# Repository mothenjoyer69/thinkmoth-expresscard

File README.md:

# ThinkMoth Expresscard to NVMe 
An ExpressCard to NVMe adapter, except this one actually ships! 

The ThinkMoth ExpressCard to NVMe is a low cost, open source adapter for using an M.2 2230/2242 NVMe SSD in an ExpressCard34/54 socket. It features a microSD card slot to enable booting from the SSD, and optional status LEDs for SD and PCIe activity so you can look at cool lights. 

Up to PCIe 3.0 @ 1x is supported (it'll be 2.0 on nearly every machine, though), and the only limitation on drives is power consumption. This board will only provide ~1a @ 3.3v, which can cause issues with higher-performance SSDs.

It also includes a yet-to-be-designed 3D printed chassis, with an EC54-specific version also in the works!

Please note that this board *only* supports NVMe drives!

Update 20/9/25:
Prototype PCBs have been ordered :) 

# More info:
1. What SSD works best?:
    - ExpressCard is super power limited with only 3v3@1A available to the SSD, so anything slower/low power drives should work fine. Higher end drives might have issues. This adapter only provides a PCIe 1x link, so there isn't much reason to get the high end drives.
2. How does booting from the SSD work?
    - Booting from the SSD works either via a bootloader being installed on the microSD card, which then loads the OS from the SSD. Alternatively, if you are able to add custom drivers, you can use the NVMe driver via Coreboot or similar for basically native operation.
3. When will it be available to buy?
    - I'm planning on having a small batch available in mid October!

# To-do
- Order intitial prototype PCBs [*]
- List on Tindie/Lectronex [ ]
- Alternate versions? [ ]

# Part list:
| Part                   | Model                        | Link                                                                               |
|------------------------|------------------------------|------------------------------------------------------------------------------------|
| ExpressCard connector  | Amphenol  10030570-2112LF    | https://www.arrow.com/en/products/10030570-2112lf/amphenol-fci                     |
| Mid-mount M.2 M-key    | Amphenol MDT180M03001        | https://www.digikey.com.au/en/products/detail/amphenol-cs-fci/MDT180M03001/5810365 |
| SD card controller     | Genesys Logic GL823K         | https://www.lcsc.com/product-detail/C284879.html                                   |
| microSD card socket    | Sofng TF-009                 | https://www.lcsc.com/product-detail/C428466.html                                   |
| 1.5A fuse              | BHFuse BSMD0805L-150         | https://www.lcsc.com/product-detail/C914095.html                                   |
| 2x 4k 6.3v resistor    | Yageo RC0402FR-073KL         | https://www.lcsc.com/product-detail/C137987.html                                   |
| 2x 0r 6.3v resistor    | Panasonic ERJ2GE0R00X        | https://www.lcsc.com/product-detail/C242160.html                                   |
| 4x 0.1uF 6.3v capacitor| Yageo CC0402KRX7R7BB104      | https://www.lcsc.com/product-detail/C60474.html                                    |
| Blue LED               | Meihua MHT192WDT-ICE         | https://www.lcsc.com/product-detail/C389522.html                                   |
| Pink LED               | Xinglight XL-1608UPC-06      | https://www.lcsc.com/product-detail/C2977076.html                                  |

# Doing it yourself:
Wanna do it yourself? Check back here after I've validated the prototype boards, and I'll have a copy of the production gerber .zip, as well as the JLCPCB order settings required!

# Credits
A very big thank you to [Ambra](https://github.com/ambraglow/) for the original board outline, cutout, and EC footprint, and also to [Wifi](https://github.com/a-little-wifi/) and [Arya](https://github.com/CRImier/) and everyone else for all of the help and advice :3

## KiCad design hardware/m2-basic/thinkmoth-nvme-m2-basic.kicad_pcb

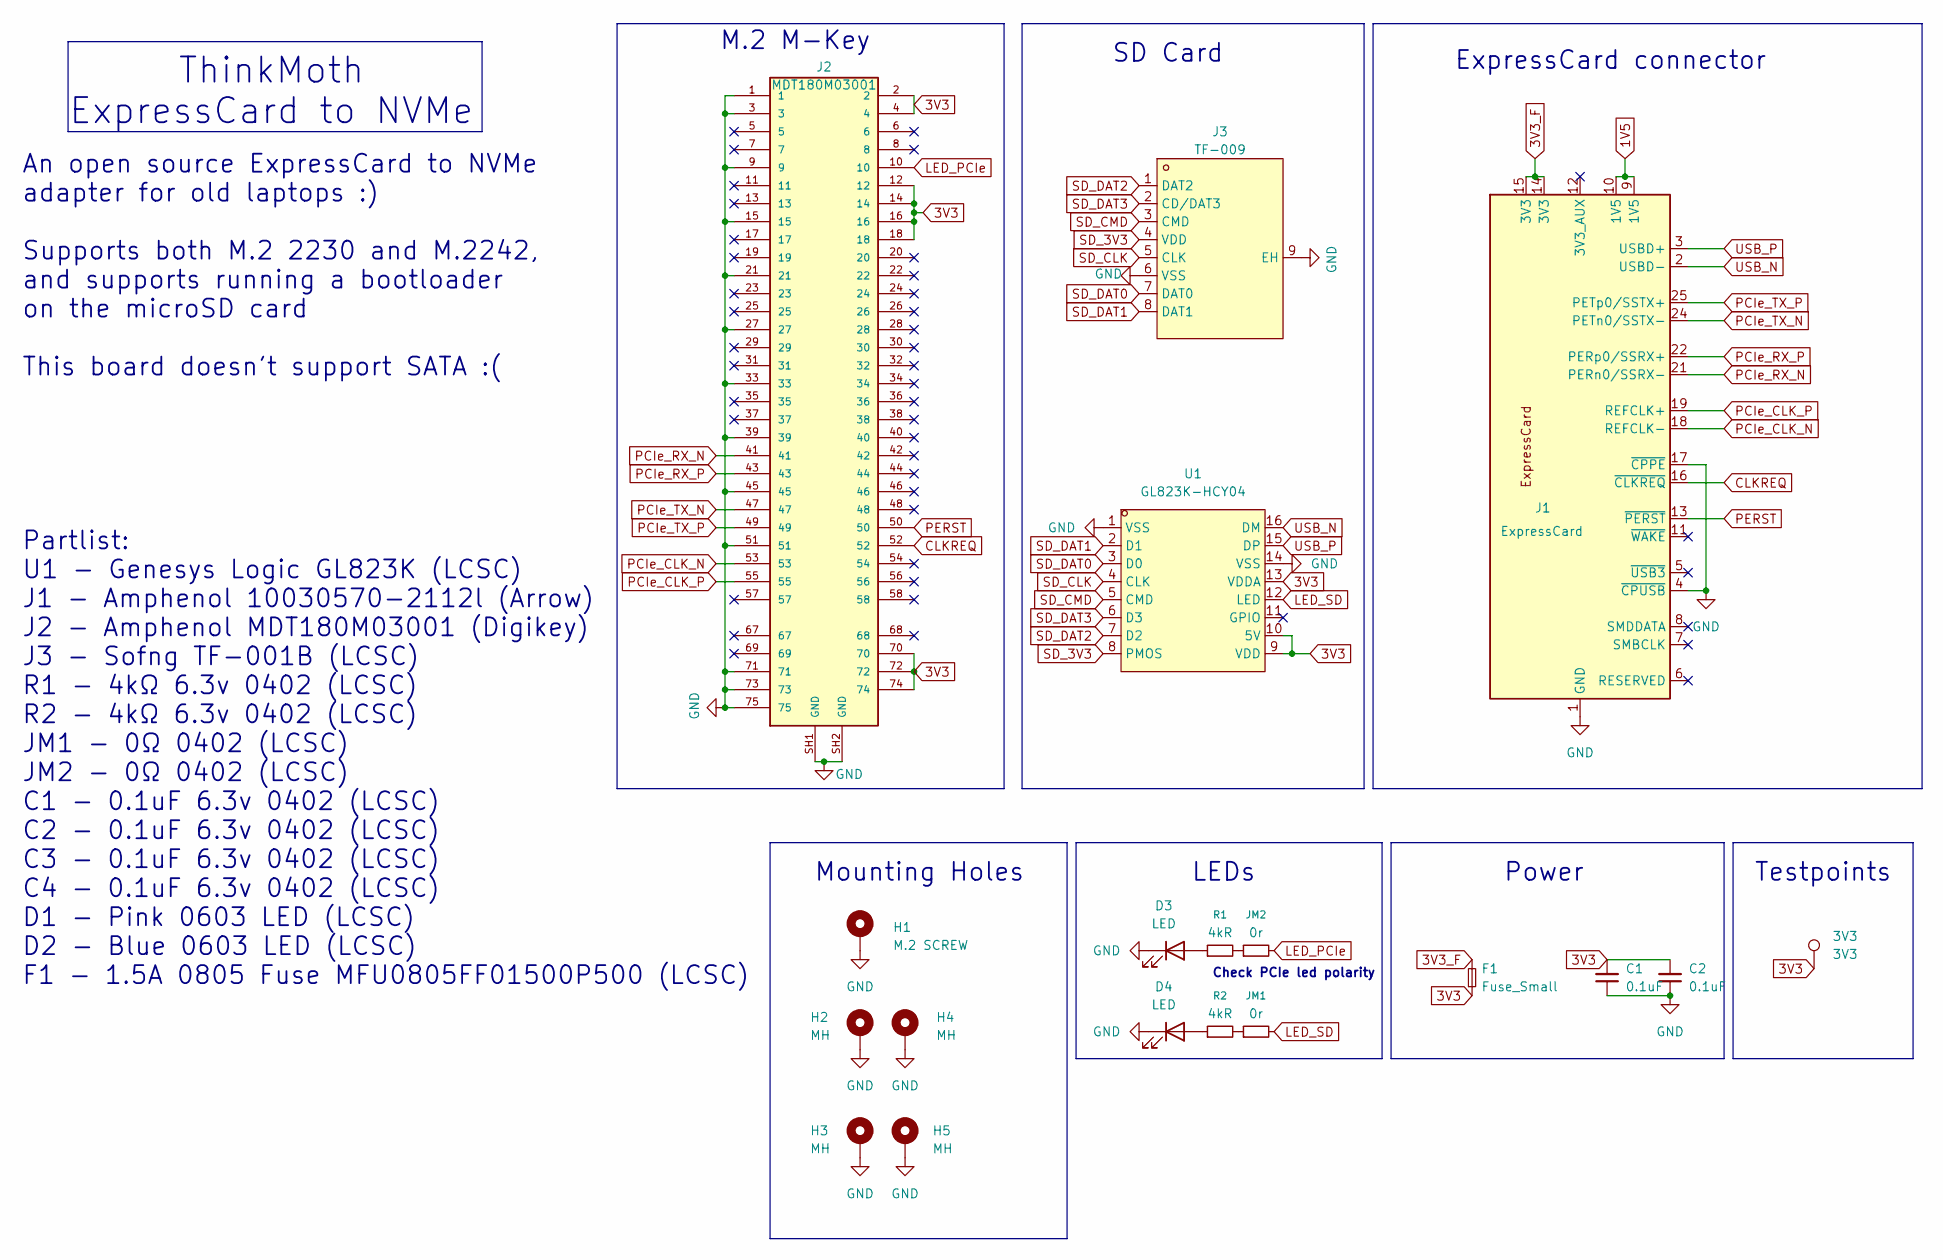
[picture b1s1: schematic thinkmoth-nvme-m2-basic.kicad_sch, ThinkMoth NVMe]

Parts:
3V3: 3V3; TestPoint_Pad_D1.0mm
C1, C2: 0.1uF; C_0402_1005Metric
D3, D4: LED; LED_0603_1608Metric
F1: Fuse_Small; Fuse_0805_2012Metric
H1: M.2 SCREW; MountingHole_2.7mm_M2.5_DIN965_Pad
H2, H3, H4, H5: MH; MountingHole_2.2mm_M2
J1: ExpressCard; ExpressCard_Plug
J2: MDT180M03001; AMPHENOL_MDT180M03001; PARTREV 2
J3: TF-009; TF-SMD_TF-009; LCSC Part C428466
JM1, JM2: 0r; R_0402_1005Metric
R1, R2: 4kR; R_0402_1005Metric
U1: GL823K-HCY04; SSOP-16_L4.9-W3.9-P0.64-LS6.0-BL; LCSC Part C284879

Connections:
1V5: J1.9 (1V5), J1.10 (1V5)
3V3: 3V3.1, C1.2, C2.2, F1.1, J2.2, J2.4, J2.12, J2.14, J2.16, J2.18, J2.70, J2.72, J2.74, U1.9 (VDD), U1.10 (5V), U1.13 (VDDA)
3V3_F: F1.2, J1.14 (3V3), J1.15 (3V3)
CLKREQ: J1.16 (~CLKREQ), J2.52
GND: C1.1, C2.1, D3.1 (K), D4.1 (K), H1.1, H2.1, H3.1, H4.1, H5.1, J1.1 (GND), J1.4 (~CPUSB), J1.17 (~CPPE), J1.20 (GND), J1.23 (GND), J1.26 (GND), J2.1, J2.3, J2.9, J2.15, J2.21, J2.27, J2.33, J2.39, J2.45, J2.51, J2.71, J2.73, J2.75, J2.SH1 (GND), J2.SH2 (GND), J3.6 (VSS), J3.9 (EH), U1.1 (VSS), U1.14 (VSS)
LED_PCIe: J2.10, JM2.2
LED_SD: JM1.2, U1.12 (LED)
unnamed: D3.2 (A), R1.1
unnamed: D4.2 (A), R2.1
unnamed: JM1.1, R2.2
unnamed: JM2.1, R1.2
PCIe_CLK_N: J1.18 (REFCLK-), J2.53
PCIe_CLK_P: J1.19 (REFCLK+), J2.55
PCIe_RX_N: J1.21 (PERn0/SSRX-), J2.41
PCIe_RX_P: J1.22 (PERp0/SSRX+), J2.43
PCIe_TX_N: J1.24 (PETn0/SSTX-), J2.47
PCIe_TX_P: J1.25 (PETp0/SSTX+), J2.49
PERST: J1.13 (~PERST), J2.50
SD_3V3: J3.4 (VDD), U1.8 (PMOS)
SD_CLK: J3.5 (CLK), U1.4 (CLK)
SD_CMD: J3.3 (CMD), U1.5 (CMD)
SD_DAT0: J3.7 (DAT0), U1.3 (D0)
SD_DAT1: J3.8 (DAT1), U1.2 (D1)
SD_DAT2: J3.1 (DAT2), U1.7 (D2)
SD_DAT3: J3.2 (CD/DAT3), U1.6 (D3)
USB_N: J1.2 (USBD-), U1.16 (DM)
USB_P: J1.3 (USBD+), U1.15 (DP)

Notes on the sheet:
ThinkMoth ExpressCard to NVMe
Mounting Holes
Power
Check PCIe led polarity
M.2 M-Key
An open source ExpressCard to NVMe adapter for old laptops :) Supports both M.2 2230 and M.2242, and supports running a bootloader on the microSD card This board doesn't support SATA :( Partlist: U1 - Genesys Logic GL823K (LCSC) J1 - Amphenol 10030570-2112l (Arrow) J2 - Amphenol MDT180M03001 (Digik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
Testpoints
LEDs
ExpressCard connector
SD Card

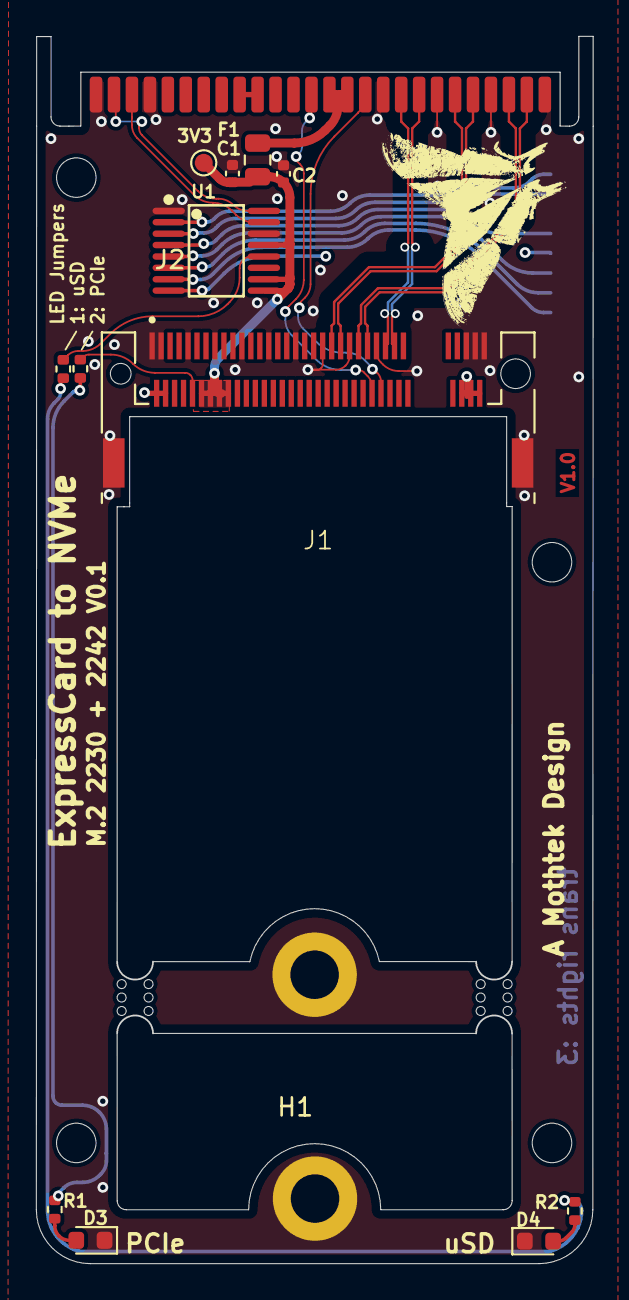
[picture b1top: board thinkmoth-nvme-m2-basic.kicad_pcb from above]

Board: 4 copper layers, 31.0 x 68.3 mm, 21 parts (1 on the bottom side), 27 nets.

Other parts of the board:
mouse-bite-2mm-slot, mouse-bite-2mm-slot#2: VAL**; mouse-bite-2mm-slot

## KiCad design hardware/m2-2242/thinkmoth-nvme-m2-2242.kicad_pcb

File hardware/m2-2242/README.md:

# ThinkMoth M.2 2242
An ExpressCard 34/54 board with support for a single M.2 2242 NVMe SSD.

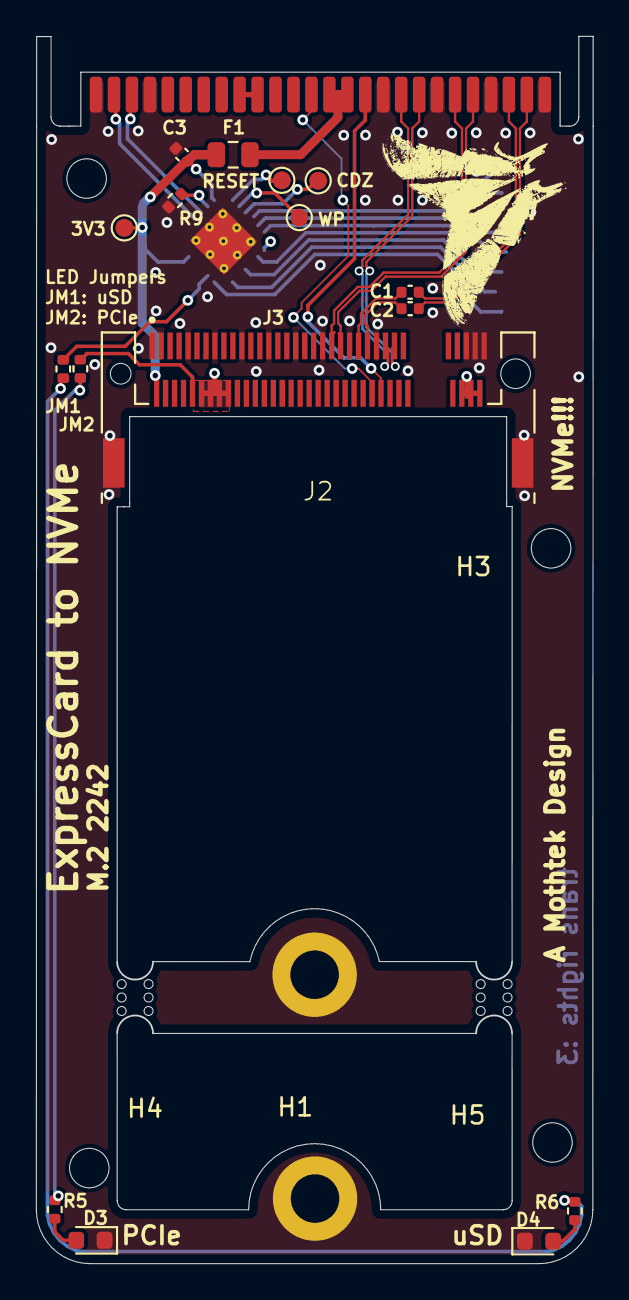
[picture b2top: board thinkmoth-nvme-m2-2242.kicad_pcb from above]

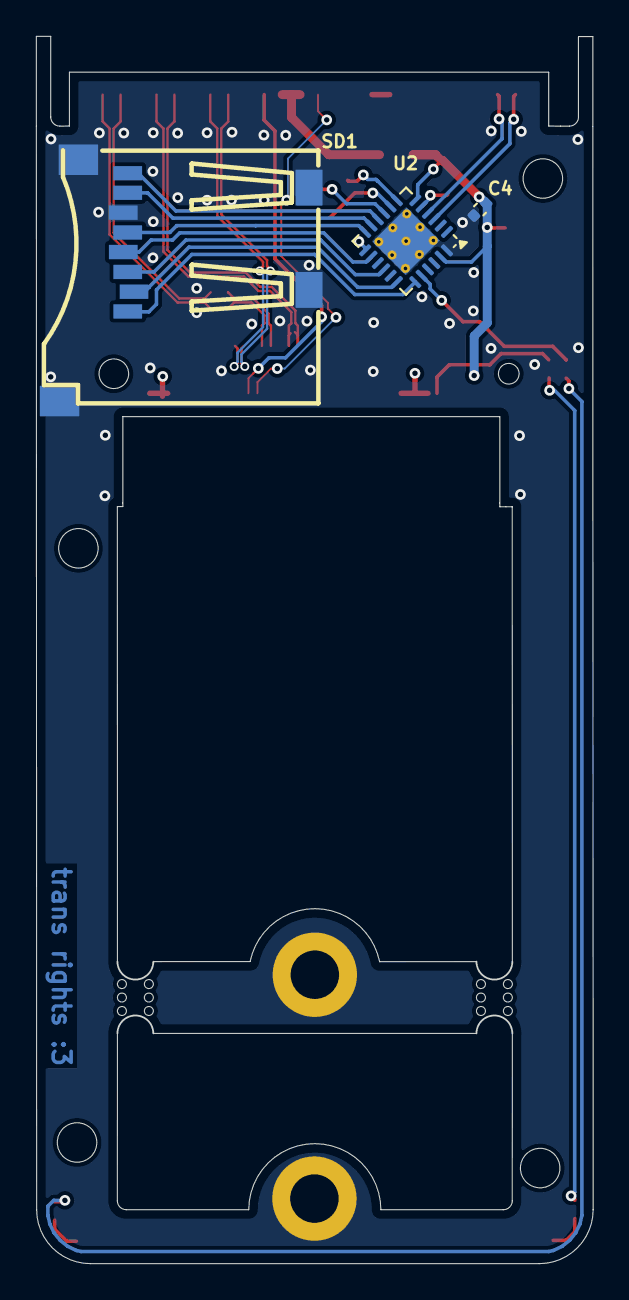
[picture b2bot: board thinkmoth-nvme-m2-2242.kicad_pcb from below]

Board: 4 copper layers, 31.0 x 68.3 mm, 27 parts (3 on the bottom side), 33 nets.

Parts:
3V3: 3V3; TestPoint_Pad_D1.0mm
C1, C2, C3, C4: 0.1uF; C_0402_1005Metric
CDZ: SD_CDZ; TestPoint_Pad_D1.0mm
D3, D4: LED; LED_0603_1608Metric
F1: Fuse_Small; Fuse_0805_2012Metric
H1: M.2 SCREW; MountingHole_2.7mm_M2.5_DIN965_Pad
H2, H3, H4, H5: MOUNTING SCREW; MountingHole_2.2mm_M2
J2: ExpressCard; ExpressCard_Plug
J3: MDT180M03001; AMPHENOL_MDT180M03001
JM1, JM2: 0r; R_0402_1005Metric
R5, R6: 4kR; R_0402_1005Metric
R9: 680r; R_0402_1005Metric
RESET: SD_RESET; TestPoint_Pad_D1.0mm
SD1: TF-001B; TF-SMD_TF-001B
U2: QFN-24-1EP_4x4mm_P0.5mm_EP2.7x2.6mm_ThermalVias
WP: SD_WP; TestPoint_Pad_D1.0mm
mouse-bite-2mm-slot, mouse-bite-2mm-slot#2: VAL**; mouse-bite-2mm-slot

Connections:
1V5: J2.9 (1V5), J2.10 (1V5)
3V3: 3V3.1, C3.2, C4.2, F1.1, J3.2, J3.4, J3.12, J3.14, J3.16, J3.18, J3.70, J3.72, J3.74, U2.6 (AVDD), U2.13 (DVDD), U2.23 (DVDD)
3V3_F: F1.2, J2.14 (3V3), J2.15 (3V3)
CLKREQ: J2.16 (~CLKREQ), J3.52
GND: C3.1, C4.1, D3.1 (K), D4.1 (K), H1.1, J2.1 (GND), J2.4 (~CPUSB), J2.17 (~CPPE), J2.20 (GND), J2.23 (GND), J2.26 (GND), J3.1, J3.3, J3.9, J3.15, J3.21, J3.27, J3.33, J3.39, J3.45, J3.51, J3.71, J3.73, J3.75, J3.SH1 (GND), J3.SH2 (GND), R9.1, SD1.6 (VSS), SD1.9 (SHIELD), SD1.10 (SHIELD), SD1.11 (SW), SD1.12 (SW), U2.24 (GND), U2.25 (GND)
unnamed: D3.2 (A), R5.1
unnamed: D4.2 (A), R6.1
unnamed: JM1.1, R6.2
unnamed: JM2.1, R5.2
unnamed: R9.2, U2.5 (RREF)
PCIe_CLK_N: J2.18 (REFCLK-), J3.53
PCIe_CLK_P: J2.19 (REFCLK+), J3.55
PCIe_LED: J3.10, JM2.2
PCIe_RX_N: J2.21 (PERn0/SSRX-), J3.41
PCIe_RX_P: J2.22 (PERp0/SSRX+), J3.43
PCIe_TX_C_N: C1.1, J2.24 (PETn0/SSTX-)
PCIe_TX_C_P: C2.1, J2.25 (PETp0/SSTX+)
PCIe_TX_N: C1.2, J3.47
PCIe_TX_P: C2.2, J3.49
PERST: J2.13 (~PERST), J3.50
SD_3V3: SD1.4 (VDD), U2.14 (PMOS)
SD_CDZ: CDZ.1, U2.9 (SD_CDZ)
SD_CLK: SD1.5 (CLK), U2.12 (SD_CLK)
SD_CMD: SD1.3 (CMD), U2.16 (SD_CMD)
SD_DAT0: SD1.7 (DAT0), U2.11 (D0)
SD_DAT1: SD1.8 (DAT1), U2.10 (D1)
SD_DAT2: SD1.1 (DAT2), U2.19 (D2)
SD_DAT3: SD1.2 (CD/DAT3), U2.18 (D3)
SD_LED: JM1.2, U2.20 (LED)
SD_RESET: RESET.1, U2.7 (RSTZ)
SD_WP: U2.8 (SD_WP), WP.1
USB_N: J2.2 (USBD-), U2.3 (DM)
USB_P: J2.3 (USBD+), U2.4 (DP)

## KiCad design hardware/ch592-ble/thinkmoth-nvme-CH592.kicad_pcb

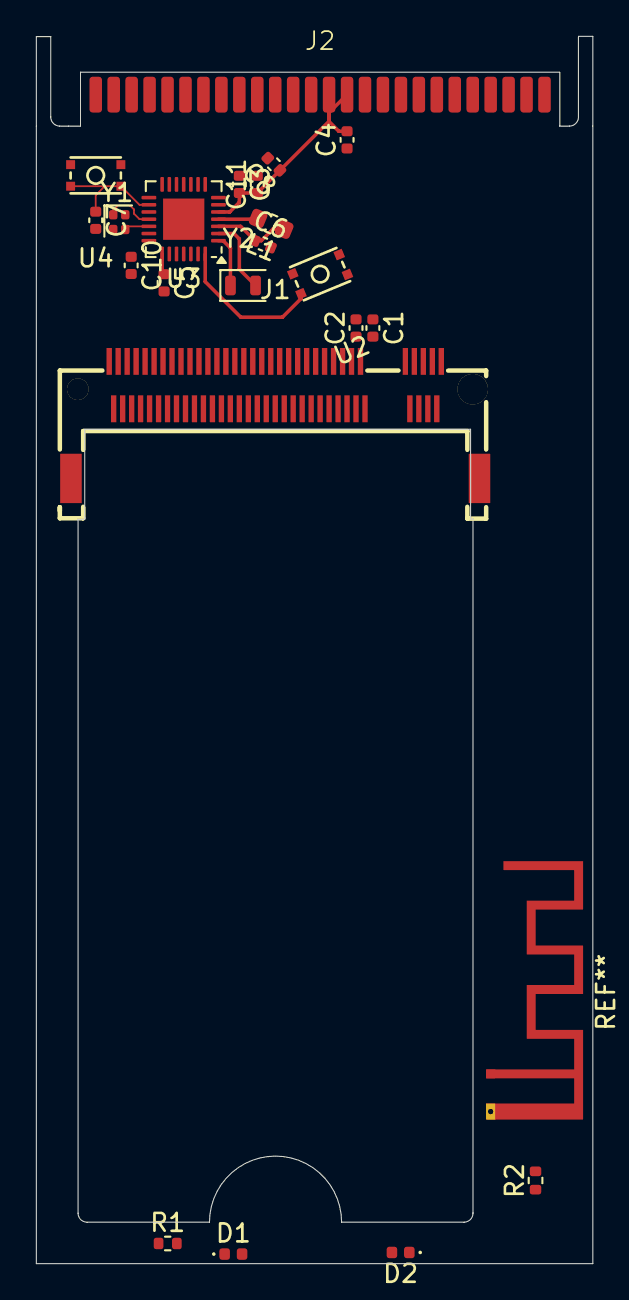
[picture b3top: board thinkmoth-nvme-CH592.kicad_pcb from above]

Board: 2 copper layers, 31.0 x 68.4 mm, 22 parts (0 on the bottom side), 28 nets.

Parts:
C1, C2, C3, C4, C8: 0.1uF; C_0402_1005Metric
C5: 2.2uF; C_0402_1005Metric
C6, C7, C10, C11: 1uF; C_0402_1005Metric
D1, D2: LED; LED_0402_1005Metric
J1: Bus_M.2_Socket_M; CONN-SMD_APCI0159-P001A
J2: ExpressCard; ExpressCard_Plug
L1: 22uH; L_0603_1608Metric
R1, R2: 680r; R_0402_1005Metric
U2: PAIR; KEY-SMD_4P-L2.8-W2.0-P1.20-LS3.0-TL
U3: QFN-28-1EP_4x4mm_P0.4mm_EP2.3x2.3mm
U4: RESET; KEY-SMD_4P-L2.8-W2.0-P1.20-LS3.0-TL
Y1: 32MHz; Crystal_SMD_1210-4Pin_1.2x1.0mm
Y2: 32.768kHz; Crystal_SMD_2012-2Pin_2.0x1.2mm

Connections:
1V5: J2.9 (1V5), J2.10 (1V5)
3V3: C3.2, C4.2, C8.1, C11.1, J2.14 (3V3), J2.15 (3V3), U3.5 (VIO33/VDD33)
CLKREQ: J1.52 (~CLKREQ), J2.16 (~CLKREQ)
GND: C3.1, C4.1, C5.2, C6.2, C7.2, C8.2, C10.2, C11.2, D1.1 (K), D2.1 (K), J1.1 (GND), J1.3 (GND), J1.9 (GND), J1.15 (GND), J1.21 (GND), J1.27 (GND), J1.33 (GND), J1.39 (GND), J1.45 (GND), J1.51 (GND), J1.57 (GND), J1.71 (GND), J1.73 (GND), J1.75 (GND), J2.1 (GND), J2.20 (GND), J2.23 (GND), J2.26 (GND), U2.3 (OUT), U2.4 (OUT), U3.29 (GND), U4.3 (OUT), U4.4 (OUT), Y1.2, Y1.4
unnamed: D1.2 (A), R1.1
unnamed: D2.2 (A), R2.1
unnamed: J1.2 (3.3V), J1.4 (3.3V), J1.12 (3.3V), J1.14 (3.3V), J1.16 (3.3V), J1.18 (3.3V), J1.70 (3.3V), J1.72 (3.3V), J1.74 (3.3V)
unnamed: J2.4 (~CPUSB), J2.17 (~CPPE)
unnamed: U3.2 (PA10/X32K1), Y2.2
unnamed: U3.1 (PA11/X32K0/TMR2), Y2.1
unnamed: C5.1, C6.1, L1.1, U3.3 (VCCID), U3.22 (VDCIA)
unnamed: C10.1, U3.20 (VINTA)
unnamed: L1.2, U3.4 (VSW)
unnamed: U3.19 (X32M1), Y1.3
unnamed: U3.18 (X32MO), Y1.1
PAIR: U2.1 (IN), U2.2 (IN), U3.28 (PA12/SCS/PWM4/AIN2)
PCIe_CLK_N: J1.53 (REFCLKn), J2.18 (REFCLK-)
PCIe_CLK_P: J1.55 (REFCLKp), J2.19 (REFCLK+)
PCIe_LED: J1.10 (DAS/~DSS/~LED1), R1.2, U3.15 (PB4/RXD0/PWM7)
PCIe_RX_N: J1.41 (PERn0/SATA-B+), J2.21 (PERn0/SSRX-)
PCIe_RX_P: J1.43 (PERp0/SATA-B-), J2.22 (PERp0/SSRX+)
PCIe_TX_N: C2.1, J1.47 (PETn0/SATA-A-), J2.24 (PETn0/SSTX-)
PCIe_TX_P: C1.1, J1.49 (PETp0/SATA-A+), J2.25 (PETp0/SSTX+)
PERST: J1.50 (~PERST), J2.13 (~PERST)
RST: C7.1, U3.16 (PB23/RST/TMR0_/TXD2/PWM11), U4.1 (IN), U4.2 (IN)
USB_N: J2.2 (USBD-), U3.12 (PB11/UD+/TMR2_)
USB_P: J2.3 (USBD+), U3.13 (PB10/UD-/TMR1_)
USER_LED: R2.2, U3.14 (PB7/TXD0/PWM9)

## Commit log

2025-06-11 initial commit, add files, add readme
2025-06-12 add TE expresscard 3d model
2025-06-13 combined m.2 2230 and 2242 design, wip
2025-06-13 update symbols
2025-06-13 keeping legacy m.2 2230 design around... for now
2025-06-13 change naming + move boards to archive folder
2025-06-13 m.2-basic: updated layout, moved mounting holes
2025-06-13 add wip board render
2025-06-13 m.2-basic: slight silkscreen tweak
2025-06-13 m.2-basic: schematic clean up
2025-06-13 m.2-basic: readme update
2025-06-14 readme: updates
2025-06-15 m.2-basic: minor layout tweaks, schem update
2025-06-17 updates for prototype run
2025-06-17 updated photos
2025-09-05 minor tweaks
2025-09-22 README.md: added part list, changed some stuff
2025-11-07 Fixed PCIe caps that shouldn't exist, minor routing tweaks
